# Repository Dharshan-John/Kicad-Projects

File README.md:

# PCB-Design-

These are my PCB design files of various designs.

Initially I had few but deleted because of mistakes so putting out the correct designs in this repository.

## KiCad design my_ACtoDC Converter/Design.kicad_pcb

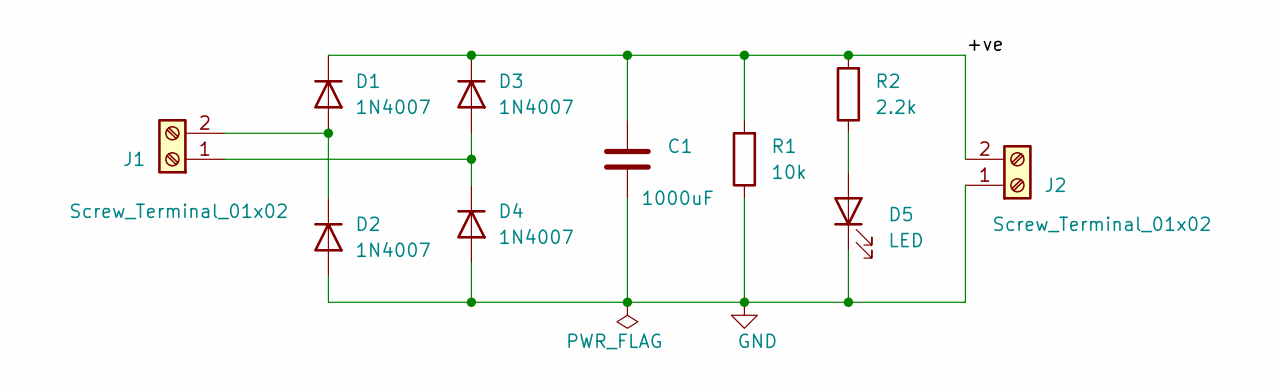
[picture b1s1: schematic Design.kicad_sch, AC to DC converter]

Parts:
C1: 1000uF; C_Radial_D8.0mm_H11.5mm_P3.50mm
D1, D2, D3, D4: 1N4007; D_DO-41_SOD81_P10.16mm_Horizontal
D5: LED; LED_D5.0mm
J1, J2: Screw_Terminal_01x02; TerminalBlock_bornier-2_P5.08mm
R1: 10k; R_Axial_DIN0207_L6.3mm_D2.5mm_P7.62mm_Horizontal
R2: 2.2k; R_Axial_DIN0207_L6.3mm_D2.5mm_P7.62mm_Horizontal

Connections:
/+ve: C1.1, D1.1 (K), D3.1 (K), J2.2, R1.2, R2.2
GND: C1.2, D2.2 (A), D4.2 (A), D5.1 (K), J2.1, R1.1
unnamed: D1.2 (A), D2.1 (K), J1.2
unnamed: D3.2 (A), D4.1 (K), J1.1
unnamed: D5.2 (A), R2.1

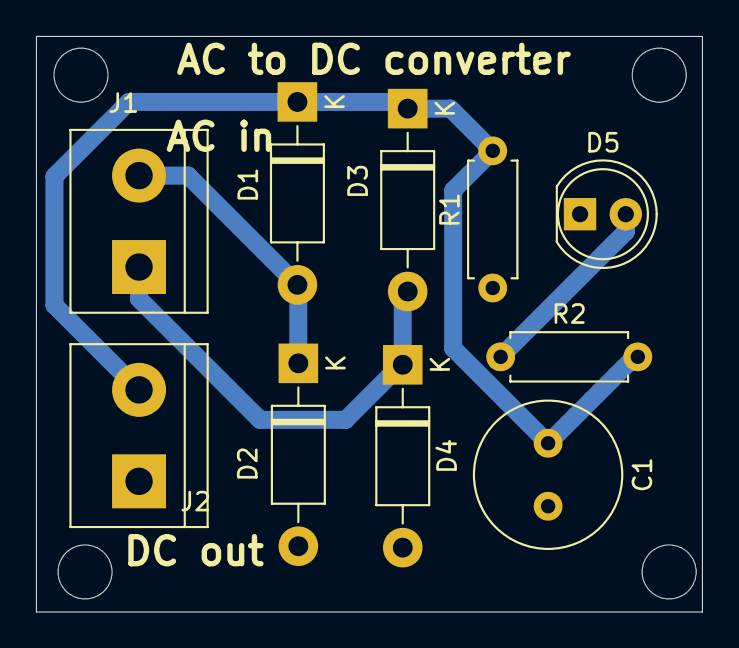
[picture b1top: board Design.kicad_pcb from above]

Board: 2 copper layers, 37.0 x 32.0 mm, 10 parts (0 on the bottom side), 5 nets.

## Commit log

2025-07-22 Create AC to DC converter
